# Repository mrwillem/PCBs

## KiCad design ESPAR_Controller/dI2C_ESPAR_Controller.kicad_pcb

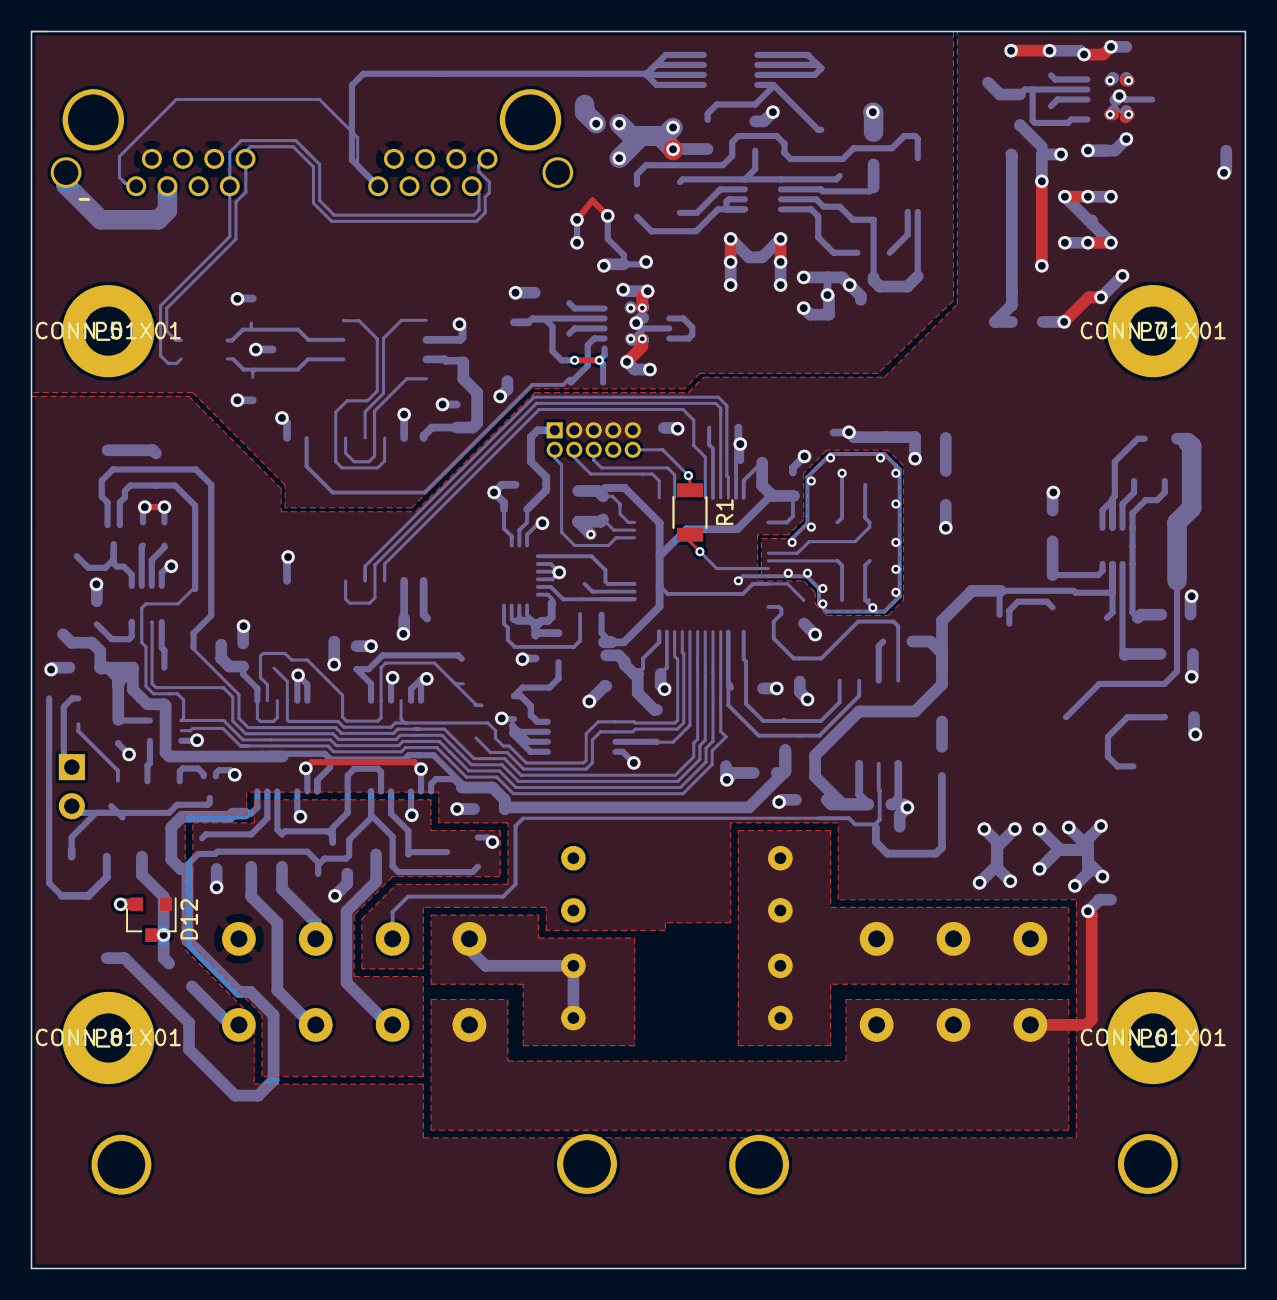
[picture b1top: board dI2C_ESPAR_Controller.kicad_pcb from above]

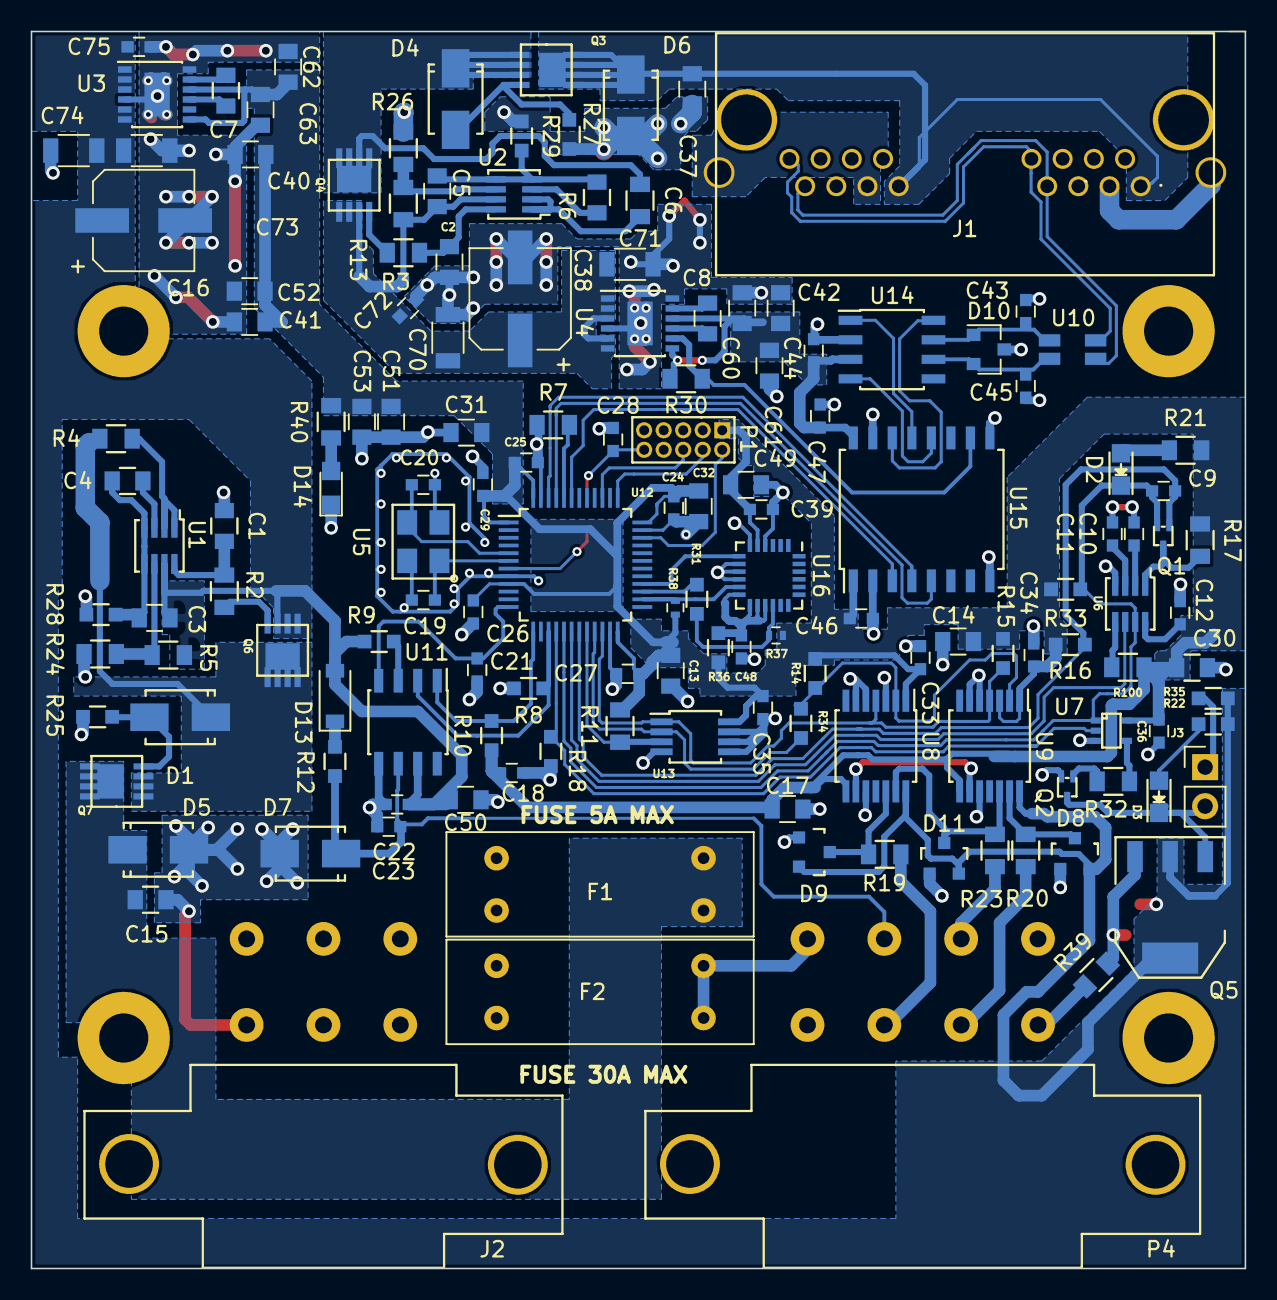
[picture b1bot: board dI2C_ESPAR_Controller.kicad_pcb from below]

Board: 4 copper layers, 79.0 x 80.5 mm, 152 parts (146 on the bottom side), 88 nets.

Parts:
C1, C2: 2nFC; C_0805
C3, C5: 470nF; C_0805
C4, C6, C50: 1uF; C_0805
C7, C8: 1uF 0805ZC105KAT2A; C_0805
C9, C10, C11, C12, C18, C21, C22, C23, C24, C25, C26, C27, C28, C29, C33, C34, C35, C36, C39, C43, C44, C45, C46, C47, C48, C72, C75: 100nF; C_0603
C13, C14, C17, C31, C49: 4,7uF; C_0805
C15, C37: 100pF 60V; C_0805
C16, C38: 33uF; CP_Elec_6.3x7.7
C19, C20: 22pF; C_0603
C30, C60, C61, C62, C63: 10uF; C_0805
C32: 2,2uF; C_0805
C40, C42, C53: 1uF GRM219R71E105KA88D; C_0805
C41: 10nF; C_0805
C51: 100nF; C_0805
C52: 1nF; C_0805
C70, C71, C73, C74: 4.7uF GRM31CR71H47; C_1206
D1, D4, D7: ZENER; SMA_Standard
D2, D3, D14: LED; LED_0805
D5, D6: D_TVS; SMA_Standard
D8, D9, D11, D12: D_Schottky_x2_Serial_AKC; SOT-23
D10: D_Schottky_x2_ACom_KKA; SOT-23
D13: D; D_SOD-123
F1, F2: FUSE; Keystone_3557_2
J1: RJHSE-5380-02; RJHSE538X-02-noled
J2: CONN_02X03; TE_JPT_2x03_PCBMOUNT
J3: CONN_01X02; Pin_Header_Straight_1x02_Pitch2.54mm
P1: CONN_5X2; Pin_Header_Straight_2x05_Pitch1.27mm
P4: CONN_02X04; TE_JPT_2x04_PCBMOUNT
P5, P6, P7, P8: CONN_01X01; hole
Q1, Q2: Q_NMOS_GSD; SOT-723
Q5: BTS4140; SOT-223
R1: 0R0; R_1206
R2, R3, R19, R20, R23, R32, R39: 10R; R_0805_HandSolder
R4, R6: 29K; R_0805_HandSolder
R5, R13: 12K; R_0805_HandSolder
R7: 10K; R_0805_HandSolder
R8, R9, R10, R18, R22, R35: 10K; R_0603_HandSolder
R11: 2K; R_0805_HandSolder
R12: 1K; R_0603_HandSolder
R14, R15: 2K; R_0603_HandSolder
R16, R25, R27, R33: 100K; R_0603_HandSolder
R17: 100K; R_0805_HandSolder
R21: 680R; R_0805_HandSolder
R24, R26: 365K; R_0805_HandSolder
R28, R29: 2K2; R_0603_HandSolder
R30: 500K; R_0805_HandSolder
R31, R34, R36: 0R0; R_0603_HandSolder
R37, R38: 2K2; R_0402
R40: R; R_0805_HandSolder
R100: 0R0; R_0805_HandSolder
SiSS71DN1, SiSS71DN2, SiSS71DN3, SiSS71DN4: SiSS71DN; PowerPack1212-8S_Pitch0.65mm
U1, U2: LTC4366-2; SOT23-8
U3, U4: LTC3245; MSOP-12-1EP_3x4mm_Pitch0.65mm
U5: 8MHz; Crystal_SMD_EuroQuartz_MT-4pin_3.2x2.5mm_hand
U6: MAX6747; SOT23-8
U7: SN74LVC1G08; SC-70-5
U8, U9: MCP45HVX1; TSSOP-14_4.4x5mm_Pitch0.65mm
U10: USB-CMC-Wuerth; CMC-SMD-Wuerth
U11: SN65HVD195-Q1; SOIC-8_3.9x4.9mm_Pitch1.27mm
U12: STM32L433CC; LQFP-48_7x7mm_Pitch0.5mm
U13: MCP9808; MSOP-8_3x3mm_Pitch0.65mm
U14: TCAN330; SOIC-8_3.9x4.9mm_Pitch1.27mm
U15: ADUM1301; SOIC-16W_7.5x10.3mm_Pitch1.27mm
U16: IIS328DQTR; QFN-24_4x4mm_Pitch0.5mm_NoMask

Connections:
12-24: C15.1, D5.1, F1.1, SiSS71DN3.5, SiSS71DN3.6, SiSS71DN3.7, SiSS71DN3.8
24VPREDIODE: D1.1, R4.2, SiSS71DN1.5, SiSS71DN1.6, SiSS71DN1.7, SiSS71DN1.8, SiSS71DN3.1, SiSS71DN3.2, SiSS71DN3.3
24VVIN: C3.1, C16.1, C22.2, C50.2, C73.1, C74.1, C75.1, D8.2, D9.2, D11.2, D12.2, D13.2, Q5.2, Q5.4, R5.2, R9.1, R22.2, R35.2, SiSS71DN1.1, SiSS71DN1.2, SiSS71DN1.3, U1.7, U3.1, U3.2, U3.3, U3.5, U3.6, U8.14, U9.14, U11.7
+3.3V: C12.2, C13.1, C14.2, C17.2, C18.2, C24.1, C25.1, C26.1, C27.1, C29.1, C30.1, C31.1, C32.1, C33.1, C34.1, C35.1, C36.1, C39.1, C40.1, C41.1, C46.1, C49.1, C51.1, C52.1, C53.1, C62.2, C63.2, P1.1, R10.1, R11.1, R14.1, R15.1, R16.1, R17.1, R21.2, R33.2, R36.1, R37.1, R38.2, R40.2, R100.1, R100.2, U3.7, U3.10, U6.5, U6.8, U7.5, U8.1, U8.8, U9.1, U9.3, U9.8, U12.1, U12.9, U12.24, U12.36, U12.48, U13.8, U15.1, U16.5
ACCEL_INT1: U12.28, U16.7
AGND: D8.1, D9.1, D11.1, P4.2, U8.10, U9.10
BTS4140DRIVER: D3.1, J3.2, Q2.3, Q5.1
CANPGOOD: R30.2, U4.8, U15.10
CANPREDIODE: D4.1, R6.2, SiSS71DN2.5, SiSS71DN2.6, SiSS71DN2.7, SiSS71DN2.8, SiSS71DN4.1, SiSS71DN4.2, SiSS71DN4.3
CANRX: U12.45, U15.5
CANSHLD: J1.6, J1.14, J1.17
CANSLEEP: U12.43, U15.3
CANTX: U12.46, U15.4
CANVIN: C5.1, C38.1, C70.1, C71.1, C72.1, R13.2, SiSS71DN2.1, SiSS71DN2.2, SiSS71DN2.3, U2.7, U4.1, U4.2, U4.3, U4.5, U4.6
CANVOUT: C42.1, C44.2, C47.1, C60.2, C61.2, R30.1, U4.7, U4.10, U14.3, U15.16
DGND: C1.1, C10.2, C11.2, C12.1, C13.2, C14.1, C15.2, C16.2, C17.1, C18.1, C19.1, C20.1, C21.2, C22.1, C23.2, C24.2, C25.2, C26.2, C27.2, C28.2, C29.2, C30.2, C31.2, C32.2, C33.2, C34.2, C35.2, C36.2, C39.2, C40.2, C41.2, C46.2, C48.1, C49.2, C50.1, C51.2, C52.2, C53.2, C62.1, C63.1, C73.2, C74.2, C75.2, D5.2, D7.2, D12.1, D14.1, J2.1, J2.3, J2.5, P1.3, P1.5, P1.7, P1.9, P4.7, Q2.2, R7.1, R8.2, R18.2, R24.1, R25.1, R28.1, U3.4, U3.12, U3.13, U5.2, U5.4, U6.4, U7.3, U8.3, U8.5, U8.6, U8.9, U9.5, U9.6, U9.9, U11.5, U12.8, U12.23, U12.35, U12.47, U13.4, U13.5, U13.6, U13.7, U15.2, U15.8, U16.4, U16.6, U16.8, U16.9, U16.10
ECANH: J1.1, J1.9, U10.1
ECANL: J1.2, J1.10, U10.4
ECANV+: C37.1, D6.1, J1.8, J1.16, SiSS71DN4.5, SiSS71DN4.6, SiSS71DN4.7, SiSS71DN4.8
EXTRESET: C28.1, P1.10, R1.1
GNDD: C2.1, C37.2, C38.2, C42.2, C43.2, C44.1, C45.2, C47.2, C60.1, C61.1, C70.2, C71.2, C72.2, D6.2, D10.3, J1.3, J1.7, J1.11, J1.15, R26.1, R27.1, R29.1, U4.4, U4.12, U4.13, U14.2, U15.9, U15.15
HEATERON: R18.1, U7.2, U12.16
HEATERSTAT: C9.2, D2.1, Q1.2, R33.1, U6.7, U7.1, U12.17
HEATERSWITCH: P4.1, R39.1
KLINE_EN: R8.1, U11.2, U12.15
KLINE_RX: R10.2, U11.1, U12.13
KLINE_TX: C21.1, U11.4, U12.12
LIN: C23.1, D7.1, P4.6, R12.1, U11.6
NWAKE: R9.2, U11.3
unnamed: C1.2, R2.1, U1.8
unnamed: C2.2, R3.1, U2.8
unnamed: C3.2, C4.1, R28.2, U1.4, U1.5
unnamed: C4.2, U1.3
unnamed: C5.2, C6.1, R29.2, U2.4, U2.5
unnamed: C6.2, U2.3
unnamed: C7.1, U3.9
unnamed: C7.2, U3.11
unnamed: C8.1, U4.9
unnamed: C8.2, U4.11
unnamed: C10.1, U6.2
unnamed: C11.1, U6.3
unnamed: C19.2, U5.1, U12.6
unnamed: C20.2, U5.3, U12.5
unnamed: C43.1, D10.1, U10.2, U14.7
unnamed: C45.1, D10.2, U10.3, U14.6
unnamed: C48.2, R36.2, U16.12, U16.13, U16.14, U16.15
unnamed: D1.2, R25.2, SiSS71DN3.4
unnamed: D2.2, R21.1
unnamed: D3.2, R22.1
unnamed: D4.2, R27.2, SiSS71DN4.4
unnamed: D8.3, R20.2, U9.13
unnamed: D9.3, R19.2, U8.12
unnamed: D11.3, R23.2, U8.13, U9.12
unnamed: D12.3, Q5.3, R39.2
unnamed: D13.1, R12.2
unnamed: D14.2, R40.1
unnamed: J3.1, R35.1
unnamed: Q1.3, R17.2, U6.1
unnamed: Q2.1, R32.2
unnamed: R1.2, U12.7
unnamed: R2.2, SiSS71DN1.4
unnamed: R3.2, SiSS71DN2.4
unnamed: R4.1, U1.1, U1.2
unnamed: R6.1, U2.1, U2.2
unnamed: R7.2, U12.44
unnamed: R13.1, R26.2, U2.6
unnamed: R5.1, R24.2, U1.6
unnamed: R31.2, U12.27
unnamed: R32.1, U7.4
unnamed: U14.1, U15.13
unnamed: U14.4, U15.12
unnamed: U14.8, U15.14
SCL: R34.1, U12.21, U13.2
SCL2: R14.2, R34.2, U8.2, U9.2
SCL_3: R38.1, U12.26, U16.11
SDA: R15.2, U8.4, U9.4, U12.22, U13.1
SDA_3: R31.1, R37.2, U16.16
SET+: P4.5, R19.1
SWCLK: P1.4, U12.37
SWDIO: P1.2, U12.34
SWO: P1.6, U12.39
TEMP+: P4.3, R20.1
TEMP-: P4.4, R23.1
TEMPALERT: R11.2, U12.20, U13.3
TIMERRESET: C9.1, Q1.1, R16.2, U12.19
VHEATER: F2.1, P4.8
VKFZ: F1.2, F2.2, J2.2, J2.4, J2.6
WATCHDOG_RESET: U6.6, U12.18

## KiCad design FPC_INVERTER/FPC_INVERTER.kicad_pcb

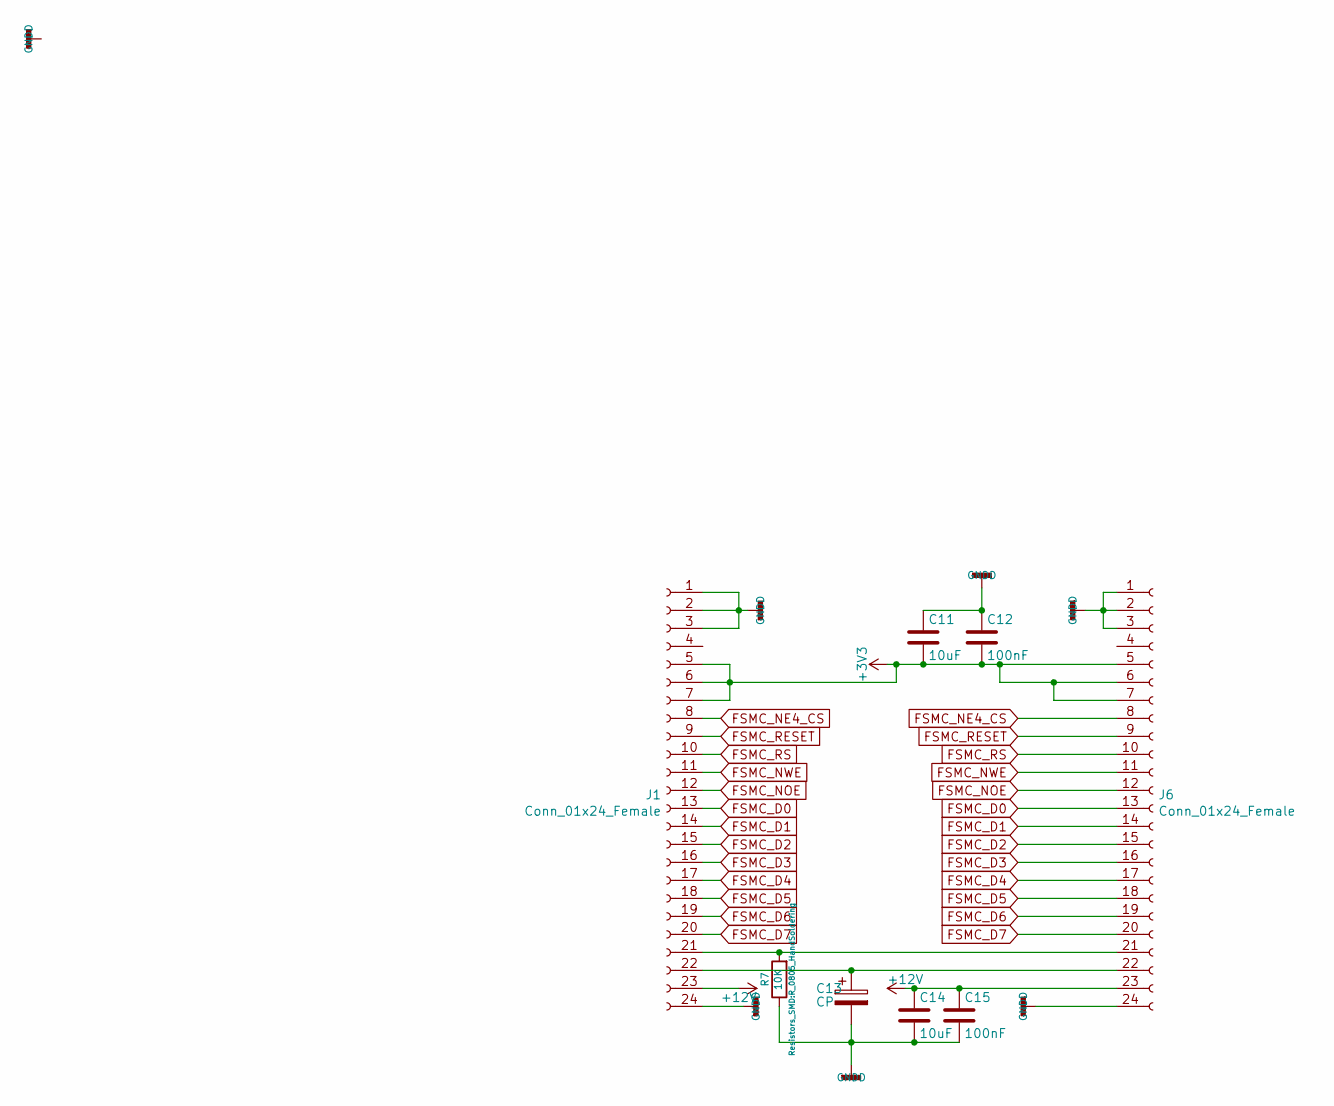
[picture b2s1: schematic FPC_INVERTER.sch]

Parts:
C11, C14: 10uF; R_0805_HandSolder
C12, C15: 100nF; R_0603_HandSolder
C13: CP; C_1210
J1, J6: Conn_01x24_Female; Hirose_FH12-24S-0.5SH_1x24-1MP_P0.50mm_Horizontal
R7: 10K; R_0805_HandSoldering

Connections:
+3V3: C11.2, C12.2, J1.5, J1.6, J1.7, J6.5, J6.6, J6.7
+12V: C14.1, C15.1, J1.23, J6.23
FSMC_D0: J1.13, J6.13
FSMC_D1: J1.14, J6.14
FSMC_D2: J1.15, J6.15
FSMC_D3: J1.16, J6.16
FSMC_D4: J1.17, J6.17
FSMC_D5: J1.18, J6.18
FSMC_D6: J1.19, J6.19
FSMC_D7: J1.20, J6.20
FSMC_NE4_CS: J1.8, J6.8
FSMC_NOE: J1.12, J6.12
FSMC_NWE: J1.11, J6.11
FSMC_RESET: J1.9, J6.9
FSMC_RS: J1.10, J6.10
GNDD: C11.1, C12.1, C13.2, C14.2, C15.2, J1.1, J1.2, J1.3, J1.24, J6.1, J6.2, J6.3, J6.24, R7.1
unnamed: C13.1, J1.22, J6.22
unnamed: J1.21, J6.21, R7.2

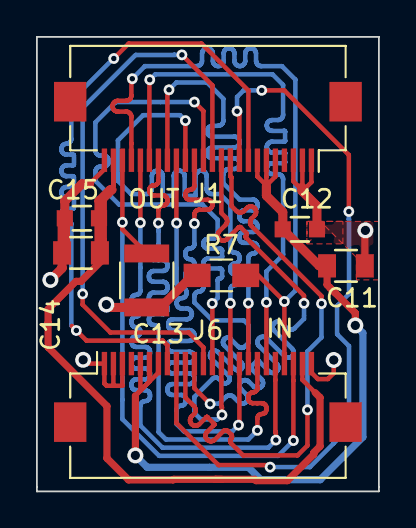
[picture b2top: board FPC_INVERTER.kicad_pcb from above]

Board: 4 copper layers, 19.0 x 25.2 mm, 8 parts (0 on the bottom side), 18 nets.

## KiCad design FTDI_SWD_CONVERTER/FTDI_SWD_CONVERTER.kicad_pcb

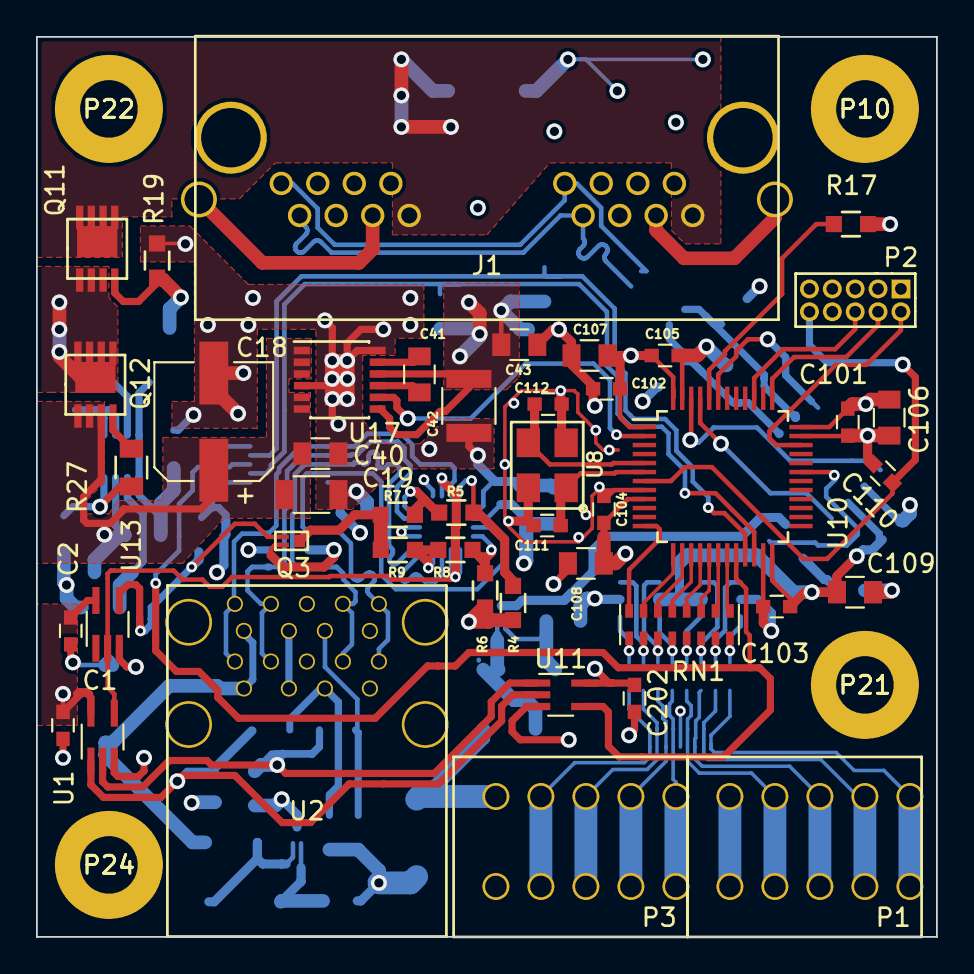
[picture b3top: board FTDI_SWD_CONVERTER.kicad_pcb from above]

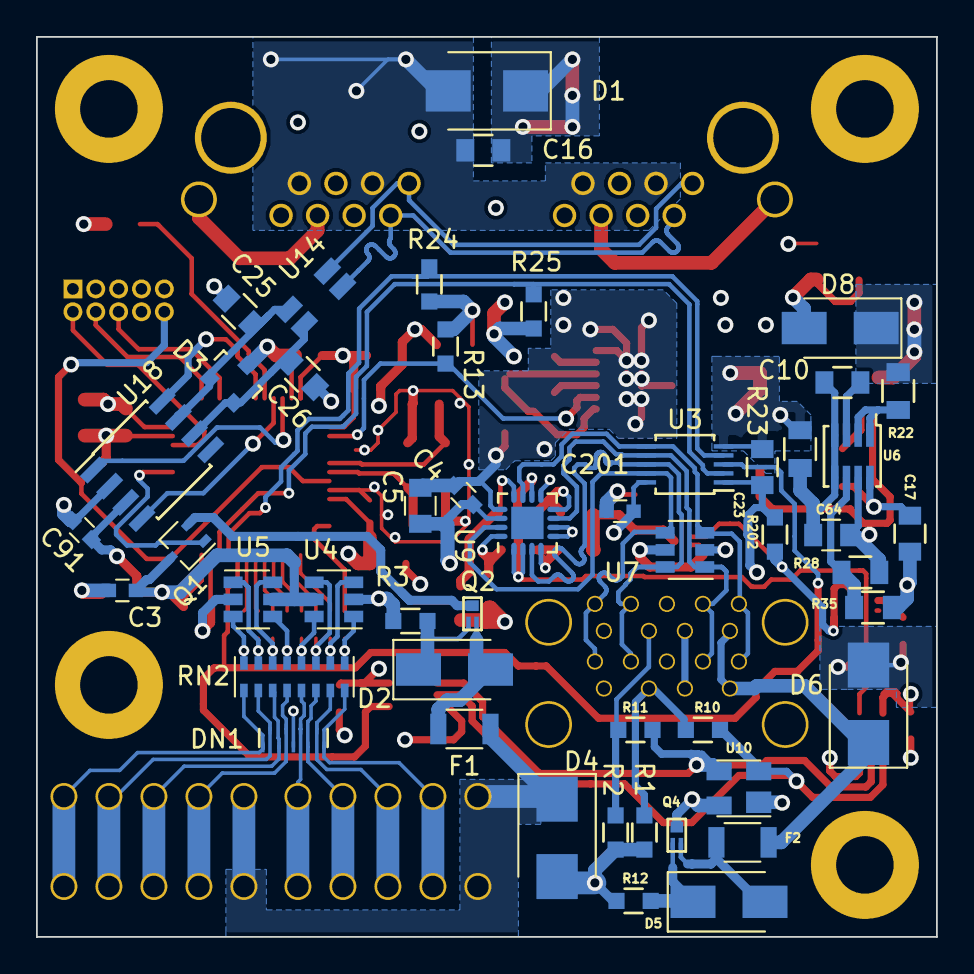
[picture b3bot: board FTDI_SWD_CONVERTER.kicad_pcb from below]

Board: 4 copper layers, 50.0 x 50.0 mm, 98 parts (49 on the bottom side), 81 nets.

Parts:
C1, C4, C91, C101, C102, C103, C104, C105, C110, C201, C202: 100nF; C_0603
C2, C3: C; C_0603
C5, C10: 1uF; C_0805
C16: 100pF 60V; C_0805
C17: 2nFC; C_0805
C18: 33uF; CP_Elec_6.3x7.7
C19: 4.7uF GRM31CR71H47; C_1206
C23, C25, C26, C40: 100nF; C_0805
C41: 1uF 0805ZC105KAT2A; C_0805
C42: 10uF; C_1210
C43: 1uF GRM219R71E105KA88D; C_0805
C64: 470nF; C_0805
C106, C108: 2,2uF; C_0805
C107, C109: 4,7uF; C_0805
C111, C112: 22pF; C_0603
D1, D4, D6: D_TVS; D_SMB_Standard
D2, D5: D; D_SMA_Standard
D3: D_Schottky_x2_ACom_KKA; SOT-23
D8: ZENER; D_SMA_Standard
DN1: SP7538P; JEDEC_MO-229
F1, F2: PTS120660V005; R_1206
J1: RJHSE-5380-02; RJHSE538X-02-noled
P1, P3: CONN_01X05; PhoenixContact_PTSM0,5_5-2,5-H-THR
P2: CONN_02X05; Pin_Header_Straight_2x05_Pitch1.27mm
P10: P10; hole
P21: P21; hole
P22: P22; hole
P24: P24; hole
Q1: Q_NMOS_GSD; SOT-323_SC-70
Q2, Q3, Q4: DMP58D0LFB; X1-DFN1006-3
Q11, Q12: SiSS71DN; PowerPack1212-8S_Pitch0.65mm
R1, R2, R3, R12, R13, R19, R202: 100K; R_0603_HandSolder
R4, R6, R7, R9: 360R; R_0603_HandSolder
R5, R8: 120R; R_0603_HandSolder
R10, R11: R; R_0603_HandSolder
R17: 10K; R_0603_HandSolder
R22: 29K; R_0805_HandSolder
R23: 2K2; R_0805_HandSolder
R24, R25: 2K; R_0603_HandSolder
R27: 10R; R_0805_HandSolder
R28: 12K; R_0805_HandSolder
R35: 365K; R_0805_HandSolder
RN1: CAT16-471J8LF; R_Cat16-8
RN2: CAT16-272J8LF; R_Cat16-8
U1: SN74LVC1G86; SOT-353_SC-70-5_Handsoldering
U2: Dual_USB3_GSB311231HR
U3: PCA9615; TSSOP-10_3x3mm_Pitch0.5mm
U4, U5: NUP4302MR6; SOT-23-6
U6: LTC4366-2; SOT23-8
U7: WE824013; SOT-23-6
U8: 8MHz; Crystal_SMD_EuroQuartz_MT-4pin_3.2x2.5mm_hand
U9: TS3A44159; QFN-16-1EP_3x3mm_Pitch0.5mm
U10: STM32L433CC; LQFP-48_7x7mm_Pitch0.5mm
U10#2: WE8240136; SOT-143
U11: SN74LVC1G32; SOT-353_SC-70-5_Handsoldering
U13: SN74LVC1G04; SOT-353_SC-70-5_Handsoldering
U14: USB-CMC-Wuerth; CMC-SMD-Wuerth
U17: LTC3245; MSOP-12-1EP_3x4mm_Pitch0.65mm
U18: TCAN330; SOIC-8_3.9x4.9mm_Pitch1.27mm

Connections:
3V3MCU: C1.2, C2.1, C3.1, C4.1, C5.2, C23.2, C42.2, C43.1, C91.1, C101.1, C102.1, C103.1, C104.1, C105.1, C106.1, C107.1, C108.1, C109.1, C201.2, C202.2, P2.1, Q1.3, Q3.2, Q4.3, R13.2, R24.1, R25.1, R202.1, U1.5, U3.1, U3.10, U4.5, U5.5, U7.5, U9.14, U10.1, U10.9, U10.24, U10.36, U10.48, U10#2.4, U11.5, U13.5, U17.7, U17.10, U18.3
ADC1: RN1.1, U10.19
ADC2: RN1.2, U10.18
ADC3: RN1.3, U10.17
ADC4: RN1.4, U10.16
ADC5: RN1.5, U10.15
ADC6: RN1.6, U10.14
ADC7: RN1.7, U10.13
ADC8: RN1.8, U10.12
CANPGOOD: R13.1, U10.2, U17.8
CANPREDIODE: D8.1, Q11.1, Q11.2, Q11.3, Q12.5, Q12.6, Q12.7, Q12.8, R22.2
CANRX: U10.45, U18.4
CANSHLD: J1.6, J1.14, J1.17
CANSLEEP: U10.43, U18.8
CANTX: U10.46, U18.1
CANVIN: C18.1, C19.1, C40.1, C64.1, Q12.1, Q12.2, Q12.3, R28.2, U6.7, U17.1, U17.2, U17.3, U17.5, U17.6
D+1: R1.1, R10.2, U2.3
D+2: R2.1, R11.2, U2.12
D-: U2.2, U2.11
DI2C_ENABLE: U3.3, U10.20, U11.4
DSCL+: U2.8, U2.17, U3.7, U7.1, U9.7
DSCL-: U2.9, U2.18, U3.6, U7.3, U9.11
DSDA+: U2.6, U2.15, U3.8, U7.6, U9.3
DSDA-: U2.5, U2.14, U3.9, U7.4, U9.15
ECANH: J1.1, J1.9, U14.1
ECANL: J1.2, J1.10, U14.4
ECANV+: C16.1, D1.1, J1.8, J1.16, Q11.5, Q11.6, Q11.7, Q11.8
EXTRESET: C110.1, P2.10, U10.7
GNDD: C1.1, C2.2, C3.2, C4.2, C5.1, C16.2, C17.1, C18.2, C19.2, C23.1, C25.2, C26.2, C40.2, C42.1, C43.2, C91.2, C101.2, C102.2, C103.2, C104.2, C105.2, C106.2, C107.2, C108.2, C109.2, C110.2, C111.1, C112.1, C201.1, C202.1, D1.2, D3.3, D4.2, D6.2, DN1.3, J1.3, J1.7, J1.11, J1.15, P2.3, P2.5, P2.7, P2.9, R1.2, R2.2, R3.2, R4.1, R6.1, R12.2, R17.1, R19.1, R23.1, R35.1, U1.3, U2.4, U2.7, U2.13, U2.16, U3.5, U4.2, U5.2, U7.2, U8.2, U8.4, U9.5, U9.6, U9.9, U9.13, U10.8, U10.23, U10.35, U10.47, U10#2.1, U11.3, U13.3, U17.4, U17.12, U17.13, U18.2
unnamed: C10.1, C64.2, R23.2, U6.4, U6.5
unnamed: C10.2, U6.3
unnamed: C17.2, R27.1, U6.8
unnamed: C25.1, D3.1, U14.2, U18.7
unnamed: C26.1, D3.2, U14.3, U18.6
unnamed: C41.1, U17.9
unnamed: C41.2, U17.11
unnamed: C111.2, U8.1, U10.6
unnamed: C112.2, U8.3, U10.5
unnamed: D2.1, Q2.1, R3.1
unnamed: D2.2, F1.2, Q2.2
unnamed: D5.1, Q4.1, R12.1
unnamed: D5.2, F2.2, Q4.2
unnamed: D8.2, Q11.4, R19.2
unnamed: Q1.2, Q2.3
unnamed: Q3.1, R202.2, U13.4
unnamed: R4.2, R5.1, U9.12
unnamed: R5.2, R7.1, U9.8
unnamed: R6.2, R8.1, U9.16
unnamed: R8.2, R9.1, U9.4
unnamed: R10.1, U1.1, U10#2.2, U11.2
unnamed: R11.1, U1.2, U10#2.3, U11.1
unnamed: R17.2, U10.44
unnamed: R22.1, U6.1, U6.2
unnamed: Q12.4, R27.2
unnamed: R28.1, R35.2, U6.6
OUT1: DN1.1, P1.5, RN2.9
OUT2: DN1.9, P1.4, RN2.10
OUT3: DN1.2, P1.3, RN2.11
OUT4: DN1.8, P1.2, RN2.12
OUT5: DN1.7, P3.5, RN2.13
OUT6: DN1.4, P3.4, RN2.14
OUT7: DN1.6, P3.3, RN2.15
OUT8: DN1.5, P3.2, RN2.16
OUTP1: RN1.16, RN2.8, U5.3
OUTP2: RN1.15, RN2.7, U5.1
OUTP3: RN1.14, RN2.6, U5.6
OUTP4: RN1.13, RN2.5, U5.4
OUTP5: RN1.12, RN2.4, U4.6
OUTP6: RN1.11, RN2.3, U4.4
OUTP7: RN1.10, RN2.2, U4.3
OUTP8: RN1.9, RN2.1, U4.1
SCL: R24.2, U3.4, U10.21
SDA: R25.2, U3.2, U10.22
SWCLK: P2.4, U10.37
SWDIO: P2.2, U10.34
SWO: P2.6, U10.39
TERMV: Q3.3, R7.2, R9.2
TERM_SWITCH: U1.4, U9.1, U9.2, U9.10, U13.2
VBUS: D6.1, F2.1, U2.1, U2.10
VSENSE: D4.1, F1.1, P1.1, P3.1
VSENSE_SWITCH: Q1.1, U10.31

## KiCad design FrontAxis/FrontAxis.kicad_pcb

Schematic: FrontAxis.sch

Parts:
C1, C3, C15, C16, C35: 100n; C_0805
C2, C4, C44, C45, C46, C47, C48, C49, C52, C53, C54, C55, C61: 10u; c_elec_4x5.8
C5, C6, C7, C8, C9, C10, C11, C12, C13, C14, C17, C18, C19, C20, C21, C22, C27, C30, C31, C32, C33, C34, C37, C38, C60: 100nF; C_0805
C23, C24, C25, C26, C40, C41, C42, C43: 5u; c_elec_4x5.8
C28, C29: 22pF; C_0805
C36: 56pF; C_0805
C39: 10uF; C_0805
C50, C51: 100 nF; C_0805
C56, C57: 10uF; C_0805_HandSoldering
C58: 10nF; C_0805_HandSoldering
C59: 1uF; C_0805_HandSoldering
D1, D2, D3, D4, D5, D6, D7, D8, D9, D10, D11, D12, D13, D14, D15, D16, D17, D18, D19, D20, D21, D22, D23, D24, D25, D26, D27, D28, D29, D30, D31, D32, D33, D34, D35, D36, D37, D38, D39, D40, D41, D42, D43, D44, D45, D46, D47, D48, D49, D50, D51, D52, D53, D54, D55, D56, D57, D58, D59, D60, D61, D62, D63, D64, D65, D66, D67, D68, D69, D70, D71, D72, D73, D74, D75, D76, D77, D78, D79, D80, D81, D82, D83, D84, D85, D86, D87, D88, D89, D90, D91, D92, D93, D94, D95, D96: LED
JP1: Jumper_NC_Small; NetTie-I_Connected_SMD
L1, L2, L3: INDUCTOR; C_0805_HandSoldering
P1, P2: CONN_6
P3: CONN_5X2
P4: I2Cext
P5, P6, P7, P8, P9, P10, P11, P12, P13, P14: CONN_1; hole
R1, R2, R3, R7, R73: 2,5K
R4, R5: 100K
R6: 9,53K
R8, R9, R10: 220R
R11, R12, R13, R14, R15, R16, R17, R18, R19, R20, R21, R22, R23, R24, R25, R26, R27, R28, R29, R30, R31, R32, R33, R38, R39, R40, R41, R42, R43, R44, R45, R46, R47, R48, R49, R50, R51, R67: 10K
R34, R35, R36, R37, R52, R53, R54, R55, R56, R57, R58, R59, R60, R61, R62, R63, R64, R65, R66: 0R0
R68: ???
S1, S2, S3, S4, S6, S7, S8: ENCODER
S5, S9, S10, S11, S12, S13, S14, S15, S16: DTS-6; switch-tact-DTS-6
U1, U3, U4, U5: TLC5947DAP; MODULE
U6: TXB0104D; MODULE
U7: AS1108; MODULE
U8: STM32F103RB; LQFP64
U9, U10, U11: 7SEGMENTLED-COMMONCATODE_HDSM533_SMD_16SEP2013
U12: TLC592X; SOIC-24_7.5x15.4mm_Pitch1.27mm
U13: CRYSTAL_SMD_CERAMIC; MODULE

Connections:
+3.3V: C1.2, C3.2, C5.2, C15.2, C16.2, C30.2, C31.2, C32.2, C33.2, C34.2, C35.1, C38.1, C39.2, C44.1, C45.1, C46.1, C47.1, C48.1, C49.1, C50.1, C51.1, C52.1, C53.1, C54.1, C55.1, C56.2, C57.2, C58.2, C59.2, C61.1, L1.1, P2.1, P2.2, P3.1, R7.1, R8.1, R11.2, R12.2, R13.2, R14.2, R15.2, R16.2, R17.2, R18.2, R21.2, R22.2, R23.2, R24.2, R25.2, R26.2, R30.1, R33.1, R67.2, S12.1, S12.2, S16.1, S16.2, U1.32 (VCC), U3.32 (VCC), U4.32 (VCC), U5.32 (VCC), U6.1 (VCCA), U6.8 (OE), U8.1 (VBAT), U8.13 (VDDA), U8.19 (VDD), U8.32 (VDD), U8.48 (VDD), U8.64 (VDD), U12.24 (VDD)
+5V: C2.2, C4.1, C6.1, C23.1, C24.1, C25.1, C26.1, C27.2, C40.1, C41.1, C42.1, C43.1, C60.2, D1.1 (A), D2.1 (A), D3.1 (A), D4.1 (A), D5.1 (A), D6.1 (A), D7.1 (A), D8.1 (A), D9.1 (A), D10.1 (A), D11.1 (A), D12.1 (A), D13.1 (A), D14.1 (A), D15.1 (A), D16.1 (A), D17.1 (A), D18.1 (A), D19.1 (A), D20.1 (A), D21.1 (A), D22.1 (A), D23.1 (A), D24.1 (A), D25.1 (A), D26.1 (A), D27.1 (A), D28.1 (A), D29.1 (A), D30.1 (A), D31.1 (A), D32.1 (A), D33.1 (A), D34.1 (A), D35.1 (A), D36.1 (A), D37.1 (A), D38.1 (A), D39.1 (A), D40.1 (A), D41.1 (A), D42.1 (A), D43.1 (A), D44.1 (A), D45.1 (A), D46.1 (A), D47.1 (A), D48.1 (A), D49.1 (A), D50.1 (A), D51.1 (A), D52.1 (A), D53.1 (A), D54.1 (A), D55.1 (A), D56.1 (A), D57.1 (A), D58.1 (A), D59.1 (A), D60.1 (A), D61.1 (A), D62.1 (A), D63.1 (A), D64.1 (A), D65.1 (A), D66.1 (A), D67.1 (A), D68.1 (A), D69.1 (A), D70.1 (A), D71.1 (A), D72.1 (A), D73.1 (A), D74.1 (A), D75.1 (A), D76.1 (A), D77.1 (A), D78.1 (A), D79.1 (A), D80.1 (A), D81.1 (A), D82.1 (A), D83.1 (A), D84.1 (A), D85.1 (A), D86.1 (A), D87.1 (A), D88.1 (A), D89.1 (A), D90.1 (A), D91.1 (A), D92.1 (A), D93.1 (A), D94.1 (A), D95.1 (A), D96.1 (A), L2.1, L3.1, P2.5, P2.6, R6.1, U6.14 (VCCB), U7.16 (VDD)
/LED0: D1.2 (K), U12.9 (OUT4)
/LED1: D2.2 (K), U12.10 (OUT5)
/LED2: D3.2 (K), U12.11 (OUT6)
/LED3: D4.2 (K), U12.12 (OUT7)
/LED4: D5.2 (K), U12.8 (OUT3)
/LED5: D6.2 (K), U12.7 (OUT2)
/LED6: D7.2 (K), U12.13 (OUT8)
/LED7: D8.2 (K), U12.14 (OUT9)
/LED8: D9.2 (K), U12.15 (OUT11)
/LED9: D10.2 (K), U12.16 (OUT12)
/LED10: D11.2 (K), U12.17 (OUT13)
/LED11: D12.2 (K), U12.18 (OUT14)
/LED12: D49.2 (K), U1.21 (OUT16)
/LED13: D50.2 (K), U1.22 (OUT17)
/LED14: D51.2 (K), U1.28 (OUT23)
/LED15: D52.2 (K), U1.27 (OUT22)
/LED16: D53.2 (K), U1.26 (OUT21)
/LED17: D54.2 (K), U1.25 (OUT20)
/LED18: D55.2 (K), U1.24 (OUT19)
/LED19: D56.2 (K), U1.23 (OUT18)
/LED20: D57.2 (K), U1.18 (OUT13)
/LED21: D58.2 (K), U1.17 (OUT12)
/LED22: D59.2 (K), U1.19 (OUT14)
/LED23: D60.2 (K), U1.20 (OUT15)
/LED24: D13.2 (K), U1.13 (OUT8)
/LED25: D14.2 (K), U1.14 (OUT9)
/LED26: D15.2 (K), U1.16 (OUT11)
/LED27: D16.2 (K), U1.15 (OUT10)
/LED28: D17.2 (K), U1.10 (OUT5)
/LED29: D18.2 (K), U1.9 (OUT4)
/LED30: D19.2 (K), U1.8 (OUT3)
/LED31: D20.2 (K), U1.7 (OUT2)
/LED32: D21.2 (K), U1.6 (OUT1)
/LED33: D22.2 (K), U1.5 (OUT0)
/LED34: D23.2 (K), U1.11 (OUT6)
/LED35: D24.2 (K), U1.12 (OUT7)
/LED36: D61.2 (K), U3.21 (OUT16)
/LED37: D62.2 (K), U3.22 (OUT17)
/LED38: D63.2 (K), U3.28 (OUT23)
/LED39: D64.2 (K), U3.27 (OUT22)
/LED40: D65.2 (K), U3.26 (OUT21)
/LED41: D66.2 (K), U3.25 (OUT20)
/LED42: D67.2 (K), U3.24 (OUT19)
/LED43: D68.2 (K), U3.23 (OUT18)
/LED44: D69.2 (K), U3.18 (OUT13)
/LED45: D70.2 (K), U3.17 (OUT12)
/LED46: D71.2 (K), U3.19 (OUT14)
/LED47: D72.2 (K), U3.20 (OUT15)
/LED48: D25.2 (K), U3.13 (OUT8)
/LED49: D26.2 (K), U3.14 (OUT9)
/LED50: D27.2 (K), U3.16 (OUT11)
/LED51: D28.2 (K), U3.15 (OUT10)
/LED52: D29.2 (K), U3.10 (OUT5)
/LED53: D30.2 (K), U3.9 (OUT4)
/LED54: D31.2 (K), U3.8 (OUT3)
/LED55: D32.2 (K), U3.7 (OUT2)
/LED56: D33.2 (K), U3.6 (OUT1)
/LED57: D34.2 (K), U3.5 (OUT0)
/LED58: D35.2 (K), U3.11 (OUT6)
/LED59: D36.2 (K), U3.12 (OUT7)
/LED60: D73.2 (K), U4.21 (OUT16)
/LED61: D74.2 (K), U4.22 (OUT17)
/LED62: D75.2 (K), U4.28 (OUT23)
/LED63: D76.2 (K), U4.27 (OUT22)
/LED64: D77.2 (K), U4.26 (OUT21)
/LED65: D78.2 (K), U4.25 (OUT20)
/LED66: D79.2 (K), U4.24 (OUT19)
/LED67: D80.2 (K), U4.23 (OUT18)
/LED68: D81.2 (K), U4.18 (OUT13)
/LED69: D82.2 (K), U4.17 (OUT12)
/LED70: D83.2 (K), U4.19 (OUT14)
/LED71: D84.2 (K), U4.20 (OUT15)
/LED72: D37.2 (K), U4.13 (OUT8)
/LED73: D38.2 (K), U4.14 (OUT9)
/LED74: D39.2 (K), U4.16 (OUT11)
/LED75: D40.2 (K), U4.15 (OUT10)
/LED76: D41.2 (K), U4.10 (OUT5)
/LED77: D42.2 (K), U4.9 (OUT4)
/LED78: D43.2 (K), U4.8 (OUT3)
/LED79: D44.2 (K), U4.7 (OUT2)
/LED80: D45.2 (K), U4.6 (OUT1)
/LED81: D46.2 (K), U4.5 (OUT0)
/LED82: D47.2 (K), U4.11 (OUT6)
/LED83: D48.2 (K), U4.12 (OUT7)
/LED84: D85.2 (K), U5.13 (OUT8)
/LED85: D86.2 (K), U5.14 (OUT9)
/LED86: D87.2 (K), U5.16 (OUT11)
/LED87: D88.2 (K), U5.15 (OUT10)
/LED88: D89.2 (K), U5.10 (OUT5)
/LED89: D90.2 (K), U5.9 (OUT4)
/LED90: D91.2 (K), U5.8 (OUT3)
/LED91: D92.2 (K), U5.7 (OUT2)
/LED92: D93.2 (K), U5.6 (OUT1)
/LED93: D94.2 (K), U5.5 (OUT0)
/LED94: D95.2 (K), U5.11 (OUT6)
/LED95: D96.2 (K), U5.12 (OUT7)
BLANK: R54.1, R56.2, R58.2, R59.2, R64.2, R67.1
BLANK1: R54.2, U8.29 (I2C2_SCL/USART3_TX/PB10)
BLANKCHANNEL: U8.17 (USART2_RX/ADC12_IN3/TIM2_CH4/PA3), U12.21 (OE)
DGND: C1.1, C2.1, C3.1, C4.2, C5.1, C6.2, C7.2, C8.2, C9.2, C10.2, C11.2, C12.2, C13.1, C14.2, C15.1, C16.1, C17.2, C18.2, C19.2, C20.2, C21.2, C22.2, C23.2, C24.2, C25.2, C26.2, C27.1, C30.1, C31.1, C32.1, C33.1, C34.1, C35.2, C36.2, C37.1, C38.2, C39.1, C40.2, C41.2, C42.2, C43.2, C44.2, C45.2, C46.2, C47.2, C48.2, C49.2, C50.2, C51.2, C52.2, C53.2, C54.2, C55.2, C56.1, C57.1, C58.1, C59.1, C60.1, C61.2, JP1.1, P1.3, P1.4, P2.3, P2.4, P3.3, P3.5, P3.7, P3.9, P4.1, P4.3, P4.5, R1.1, R2.1, R3.1, R4.1, R5.1, R9.2, R19.2, R31.2, R73.1, S1.1 (G), S2.1 (G), S3.1 (G), S4.1 (G), S6.1 (G), S7.1 (G), S8.1 (G), U1.1 (GND), U3.1 (GND), U4.1 (GND), U5.1 (GND), U6.7 (GND), U7.4 (GND), U7.7 (GND), U8.12 (VSSA), U8.18 (VSS), U8.28 (BOOT1/PB2), U8.31 (VSS), U8.47 (VSS), U8.60 (BOOT0), U8.63 (VSS), U12.1 (GND)
DISP1: U1.30 (XLAT), U8.30 (I2C2_SDA/USART3_RX/PB11)
DISP2: R35.2, U8.27 (ADC12_IN9/TIM3_CH4/PB1)
DISP3: R36.2, U8.26 (ADC12_IN8/TIM3_CH3/PB0)
DISP4: R52.2, U8.25 (PC5/ADC12_IN15)
DISP5: U8.20 (SPI1_NSS/USART2_CK/ADC12_IN4/PA4), U12.4 (LE)
I2CSCL: P4.2, U8.58 (I2C1_SCL/TIM4_CH1/PB6)
I2CSDA: P4.4, U8.59 (I2C1_SDA/TIM4_CH2/PB7)
NRST: C37.2, P3.10, U8.7 (~NRST)
unnamed: C18.1, R47.1, R53.1
unnamed: C28.1, U8.5 (PD0/OSC_IN), U13.1 (OSC)
unnamed: C29.2, R68.1, U13.3 (OSC)
unnamed: C36.1, R10.2
unnamed: L1.2, P1.5, P1.6
unnamed: L2.2, L3.2, P1.1, P1.2
unnamed: R1.2, U3.31 (IREF)
unnamed: R2.2, U4.31 (IREF)
unnamed: R3.2, U5.31 (IREF)
unnamed: R4.2, R55.1, S5.3, S5.4, S9.3, S9.4, S10.3, S10.4, S11.3, S11.4, S15.3, S15.4, S16.3, S16.4
unnamed: R6.2, U7.15 (ISET)
unnamed: R7.2, U12.23 (REXT)
unnamed: R11.1, R40.2, S1.2 (A)
unnamed: R12.1, R41.2, S1.3 (B)
unnamed: R13.1, R42.2, S2.2 (A)
unnamed: R14.1, R43.2, S2.3 (B)
unnamed: R15.1, R48.2, S3.2 (A)
unnamed: R16.1, R49.2, S3.3 (B)
unnamed: R17.1, R50.2, S4.2 (A)
unnamed: R18.1, R51.2, S4.3 (B)
unnamed: R19.1, R20.2, S5.1, S5.2
unnamed: R20.1, R27.2, S9.1, S9.2
unnamed: R21.1, R46.2, S6.2 (A)
unnamed: R22.1, R47.2, S6.3 (B)
unnamed: R23.1, R38.2, S7.2 (A)
unnamed: R24.1, R39.2, S7.3 (B)
unnamed: R25.1, R44.2, S8.2 (A)
unnamed: R26.1, R45.2, S8.3 (B)
unnamed: R27.1, R28.2, S11.1, S11.2
unnamed: R28.1, R29.2, S10.1, S10.2
unnamed: R29.1, R30.2, S15.1, S15.2
unnamed: R31.1, R32.2, S14.1, S14.2
unnamed: R32.1, R33.2, S13.1, S13.2
unnamed: R35.1, R62.2
unnamed: R36.1, R63.2
unnamed: R37.1, U6.3 (A2)
unnamed: R52.1, R66.2
unnamed: R56.1, U1.2 (BLANK)
unnamed: R57.1, U1.4 (MOSI)
unnamed: R58.1, U3.2 (BLANK)
unnamed: R59.1, U4.2 (BLANK)
unnamed: R60.1, U3.4 (MOSI)
unnamed: R61.1, U4.4 (MOSI)
unnamed: R62.1, U3.30 (XLAT)
unnamed: R63.1, U4.30 (XLAT)
unnamed: R64.1, U5.2 (BLANK)
unnamed: R65.1, U5.4 (MOSI)
unnamed: R66.1, U5.30 (XLAT)
unnamed: R68.2, U8.6 (PD1/OSC_OUT)
unnamed: R73.2, U1.31 (IREF)
unnamed: U6.11 (B3), U7.2 (DIN)
unnamed: U6.12 (B2), U7.9 (LOAD/CS)
unnamed: U6.13 (B1), U7.10 (CLK)
unnamed: U7.3 (DIG0), U9.3 (Com-Cat), U9.8 (Com-Cat)
unnamed: U7.18 (SEGE), U9.1 (An-e), U10.1 (An-e), U11.1 (An-e)
unnamed: U7.20 (SEGD), U9.2 (An-d), U10.2 (An-d), U11.2 (An-d)
unnamed: U7.8 (DIG1), U10.3 (Com-Cat), U10.8 (Com-Cat)
unnamed: U7.17 (SEGC), U9.4 (An-c), U10.4 (An-c), U11.4 (An-c)
unnamed: U7.19 (SEGDP), U9.5 (An-dp), U10.5 (An-dp), U11.5 (An-dp)
unnamed: U7.13 (SEGB), U9.6 (An-b), U10.6 (An-b), U11.6 (An-b)
unnamed: U7.11 (SEGA), U9.7 (An-a), U10.7 (An-a), U11.7 (An-a)
unnamed: U7.12 (SEGF), U9.9 (An-f), U10.9 (An-f), U11.9 (An-f)
unnamed: U7.14 (SEGG), U9.10 (An-g), U10.10 (An-g), U11.10 (An-g)
unnamed: U7.5 (DIG2), U11.3 (Com-Cat), U11.8 (Com-Cat)
R1A: C7.1, R40.1, U8.33 (SPI2_NSS/I2C2_SMBA/USART3_CK/TIM1_BKIN/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)
R1B: C8.1, R41.1, U8.34 (SPI2_SCK/USART3_CTS/TIM1_CH1N/PB13)
R2A: C9.1, R42.1, U8.35 (SPI2_MISO/USART3_RTS/TIM1_CH2N/PB14)
R2B: C10.1, R43.1, U8.36 (SPI2_MOSI/TIM1_CH3N/PB15)
R3A: C19.1, R38.1, U8.37 (PC6)
R3B: C20.1, R39.1, U8.38 (PC7)
R4A: C21.1, R44.1, U8.39 (PC8)
R4B: C22.1, R45.1, U8.40 (PC9)
R5A: C11.1, R48.1, U8.41 (USART1_CK/TIM1_CH1/MCO/PA8)
R5B: C12.1, R49.1, U8.42 (USART1_TX/TIM1_CH2/PA9)
R6A: C13.2, R50.1, U8.43 (USART1_RX/TIM1_CH3/PA10)
R6B: C14.1, R51.1, U8.44 (USART1_CTS/CANRX/USBDM/TIM1_CH4/PA11)
R7A: C17.1, R46.1, U8.45 (USART1_RTS/CANTX/USBDP/TIM1_ETR/PA12)
R7B: R53.2, U8.62 (TIM4_CH4/PB9)
SEGMENTCS: R37.2, U8.24 (PC4/ADC12_IN14)
SPI1CLK: R8.2, R9.1, R10.1, U1.3 (CLK), U3.3 (CLK), U4.3 (CLK), U5.3 (CLK), U6.2 (A1), U8.21 (SPI1_SCK/ADC12_IN5/PA5), U12.3 (CLK)
SPI1MISO: U8.22 (SPI1_MISO/ADC12_IN6/TIM3_CH1/PA6)
SPI1MOSI: R34.2, U8.23 (SPI1_MOSI/ADC12_IN7/TIM3_CH2/PA7), U12.2 (SDI)
SPIMOSI: R34.1, R57.2, R60.2, R61.2, R65.2, U6.4 (A3)
SWCLK: P3.4, U8.49 (JTCK/SWCLK/PA14)
SWDIO: P3.2, U8.46 (JTMS/SWDIO/PA13)
SWO: P3.6, U8.55 (JTDO/PB3)
SWRESET: P4.6, U8.61 (TIM4_CH3/PB8)
SWSPECIAL: R55.2, U8.16 (USART2_TX/ADC12_IN2/TIM2_CH3/PA2)
SWSTORE: R5.2, S12.3, S12.4, S13.3, S13.4, S14.3, S14.4, U8.15 (USART2_RTS/ADC12_IN1/TIM2_CH2/PA1)
xtalgnd: C28.2, C29.1, JP1.2, U13.2 (GND), U13.4 (GND)

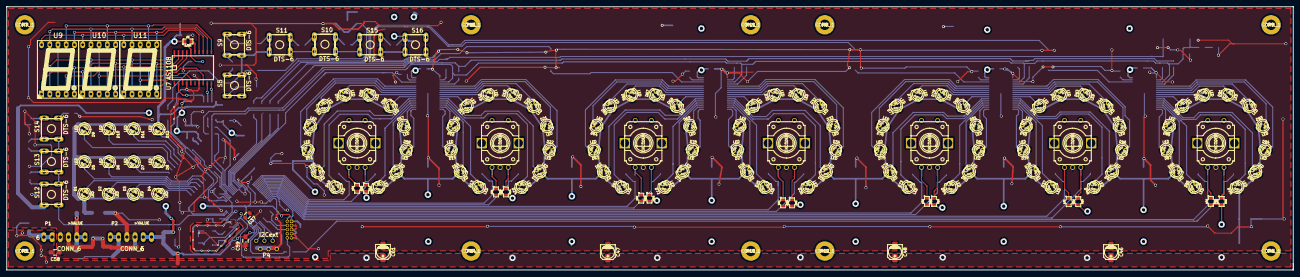
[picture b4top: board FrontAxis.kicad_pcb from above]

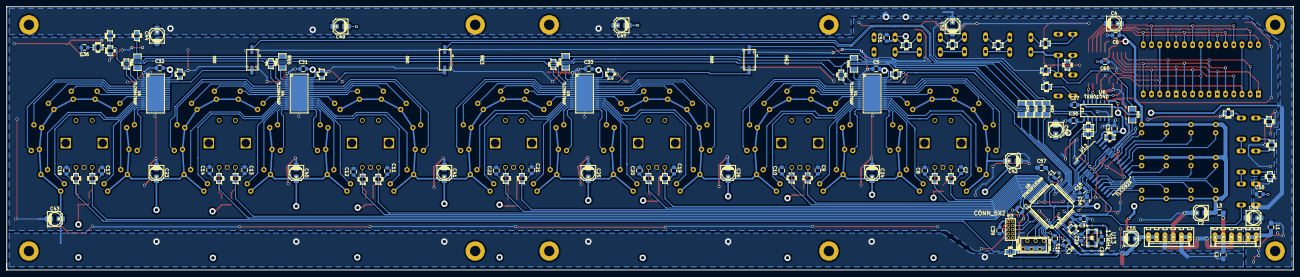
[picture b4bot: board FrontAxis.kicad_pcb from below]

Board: 4 copper layers, 397.3 x 81.3 mm, 272 parts (124 on the bottom side), 199 nets.
